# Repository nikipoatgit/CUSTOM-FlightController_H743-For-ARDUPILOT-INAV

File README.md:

# CUSTOM FlightController-H743
The repo contains flight controller target files, PCB Gerber files, and the schematic.

## FC notes 
Nickel-H473 is based on MAMBAH743_V4 FC

However custom pin can be used unless their usage is not compromised , STM programmer IDE can be a great help in case assigning pins.

## FIRMWARE SETUP 

ARDUPILOT : **https://github.com/ArduPilot/ardupilot**

Target Files :`libraries/AP_HAL_ChibiOS/hwdef/`

Environment setup : https://ardupilot.org/dev/docs/building-the-code.html

Build cmd :
```bash
./waf distclean
./Tools/scripts/build_bootloaders.py Nickel407       # Builds bootloader (outputs to Tools/bootloaders/)
./waf configure --board FlyingMoon407
./waf plane
```
bin/hex file are stored in build directory
             
It is recommended to go through ardupilot documentation First

## Target Files 

There are two primary target files ` hwdef-bl.dat (responsible for building bootloader)  
                                        hwdef.dat (for main firmware)`

Checkout this HW files for reference example :   https://github.com/ArduPilot/ardupilot/tree/master/libraries/AP_HAL_ChibiOS/hwdef/fmuv3

### For pin mapping use STM programmer IDE 

## Schematic & PCB 
Check schematic folder  
The pcb is 2 layer 47 * 60 mm

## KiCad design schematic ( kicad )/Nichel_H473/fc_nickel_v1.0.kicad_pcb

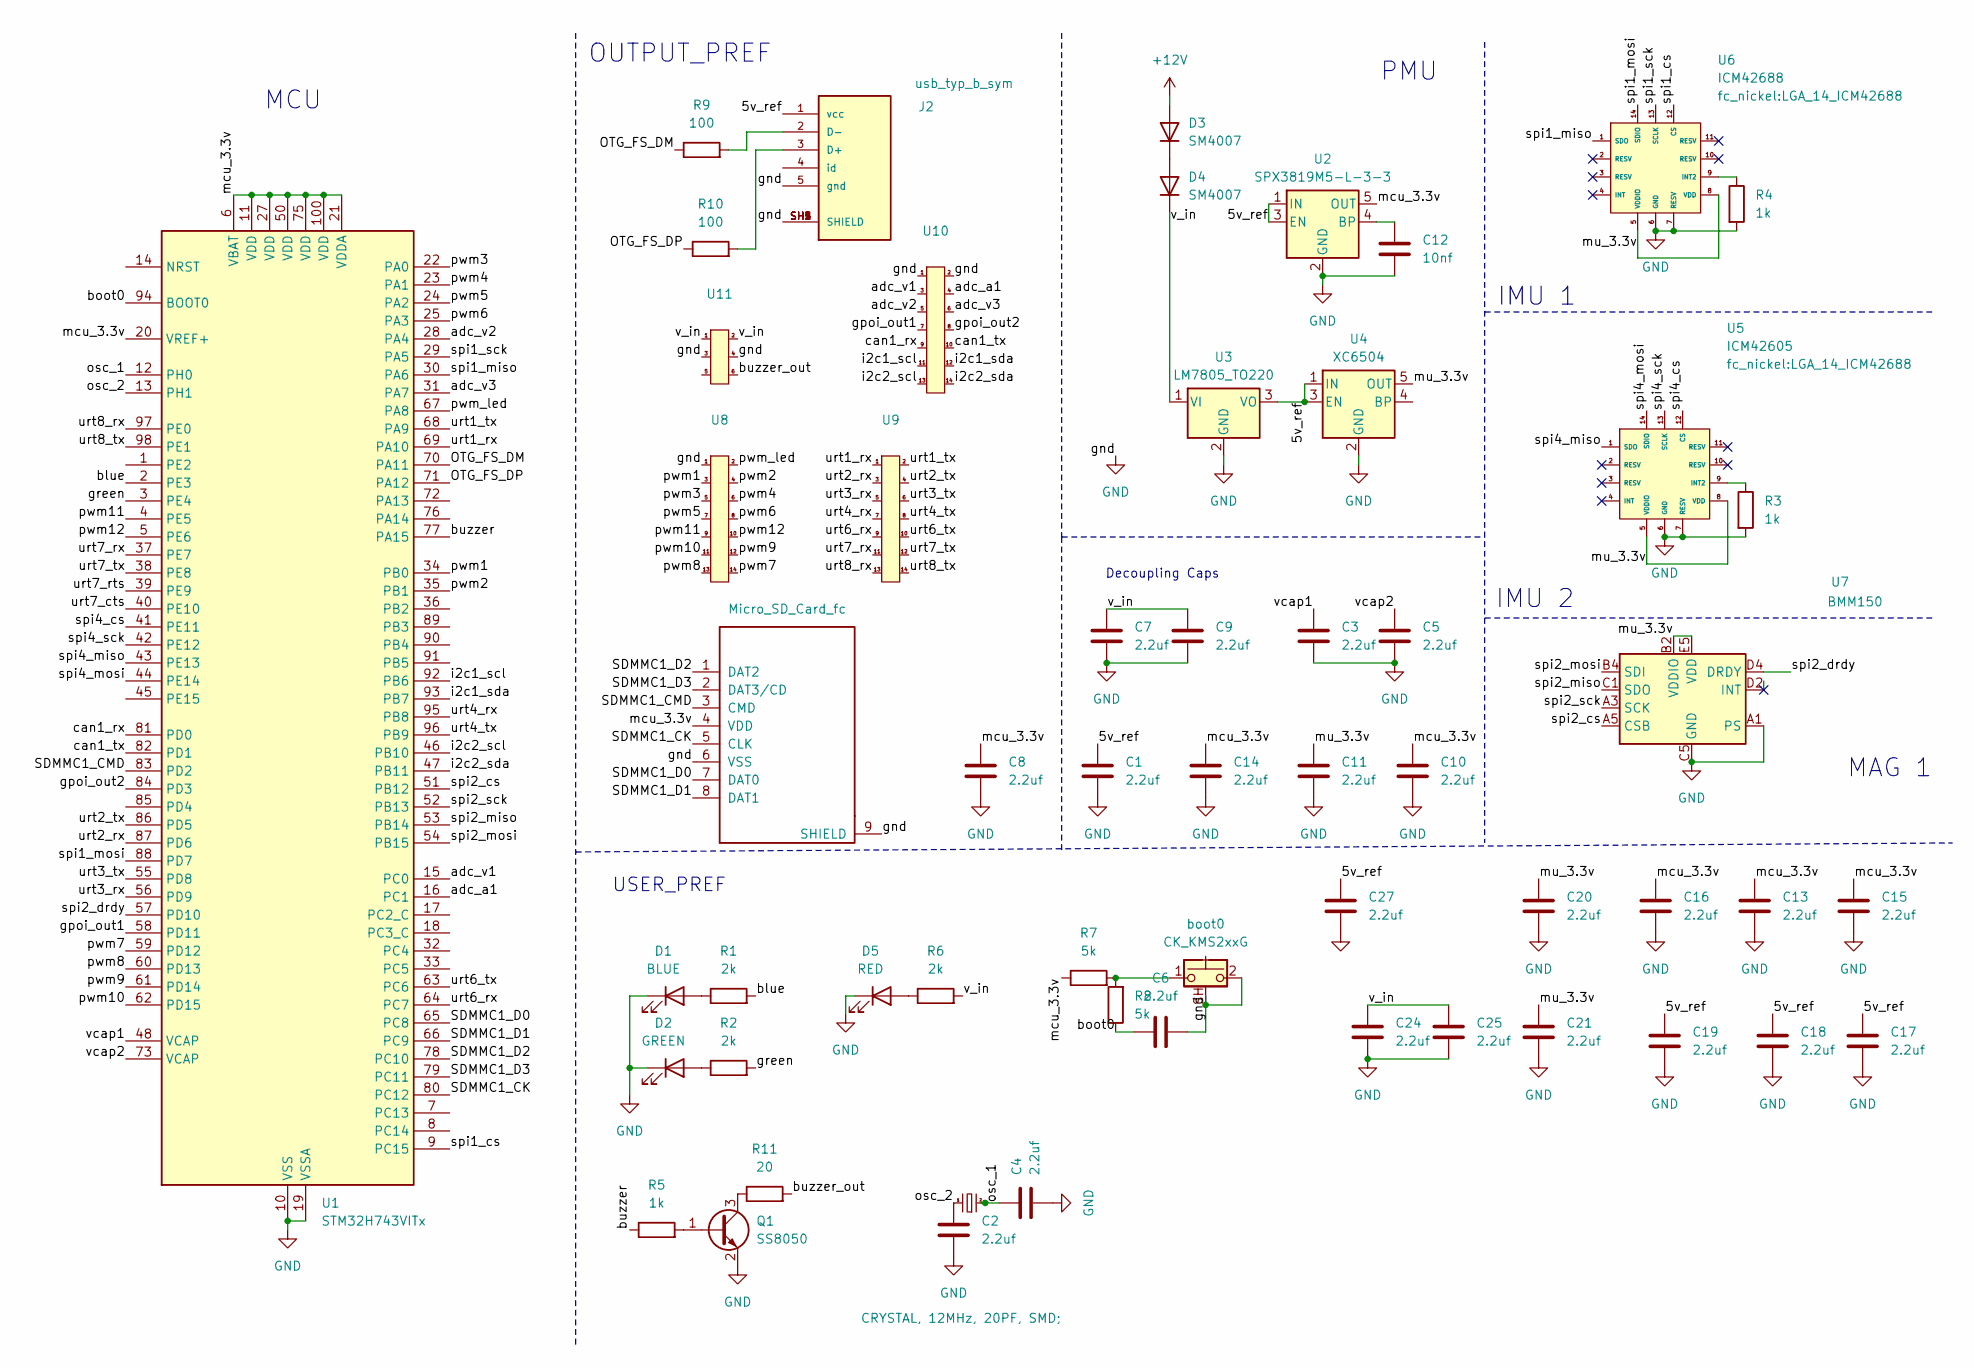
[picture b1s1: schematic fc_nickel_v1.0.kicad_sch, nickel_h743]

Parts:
C1, C2, C3, C4, C5, C6, C7, C8, C9, C10, C11, C13, C14, C15, C16, C17, C18, C19, C20, C21, C24, C25, C27: 2.2uf; C_01005_0402Metric_Pad0.57x0.30mm_HandSolder
C12: 10nf; C_01005_0402Metric_Pad0.57x0.30mm_HandSolder
D1: BLUE; LED_0402_1005Metric
D2: GREEN; LED_0402_1005Metric
D3, D4: SM4007; C_0402_1005Metric
D5: RED; LED_0402_1005Metric
J1: Micro_SD_Card_fc; micro_sdcard_new
J2: usb_typ_b_sym; usb_typ_b; PARTREV 1.0
Q1: SS8050; SOT-23
R1, R2, R6: 2k; R_0402_1005Metric
R3, R4, R5: 1k; R_0402_1005Metric
R7, R8: 5k; R_0402_1005Metric
R9, R10: 100; R_0402_1005Metric
R11: 20; R_0402_1005Metric
U1: STM32H743VITx; LQFP-100_14x14mm_P0.5mm
U2: SPX3819M5-L-3-3; SOT-23-5
U3: LM7805_TO220; TO-220-3_Vertical
U4: XC6504; SOT-23-5
U5: ICM42605; LGA_14_ICM42688
U6: ICM42688; LGA_14_ICM42688
U7: BMM150; WLCSP-12_1.56x1.56mm_P0.4mm
U8: IDC-Header_2x04_P2.54mm_fc
U9, U10: IDC-Header_P2.54mm_fc
U11: IDC-Header_2x03_P2.54mm_fc_power
Y2: CRYSTAL, 12MHz, 20PF, SMD;; XTAL1170X500X450_crystal
boot0: CK_KMS2xxG; SW_SPST_CK_KMS2xxGP

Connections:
+12V: D3.2 (A)
/5v_ref: C1.1, C17.1, C18.1, C19.1, C27.1, J2.1 (vcc), U2.1 (IN), U2.3 (EN), U3.3 (VO), U4.1 (IN), U4.3 (EN)
/OTG_FS_DM: R9.1, U1.70 (PA11)
/OTG_FS_DP: R10.1, U1.71 (PA12)
/SDMMC1_CK: J1.5 (CLK), U1.80 (PC12)
/SDMMC1_CMD: J1.3 (CMD), U1.83 (PD2)
/SDMMC1_D0: J1.7 (DAT0), U1.65 (PC8)
/SDMMC1_D1: J1.8 (DAT1), U1.66 (PC9)
/SDMMC1_D2: J1.1 (DAT2), U1.78 (PC10)
/SDMMC1_D3: J1.2 (DAT3/CD), U1.79 (PC11)
/adc_a1: U1.16 (PC1), U10.4
/adc_v1: U1.15 (PC0), U10.3
/adc_v2: U1.28 (PA4), U10.5
/adc_v3: U1.31 (PA7), U10.6
/blue: R1.2, U1.2 (PE3)
/boot0: C6.1, R8.1, U1.94 (BOOT0)
/buzzer: R5.1, U1.77 (PA15)
/buzzer_out: R11.2, U11.6
/can1_rx: U1.81 (PD0), U10.9
/can1_tx: U1.82 (PD1), U10.10
/gpoi_out1: U1.58 (PD11), U10.7
/gpoi_out2: U1.84 (PD3), U10.8
/green: R2.2, U1.3 (PE4)
/i2c1_scl: U1.92 (PB6), U10.11
/i2c1_sda: U1.93 (PB7), U10.12
/i2c2_scl: U1.46 (PB10), U10.13
/i2c2_sda: U1.47 (PB11), U10.14
/mcu_3.3v: C8.1, C10.1, C13.1, C14.1, C15.1, C16.1, J1.4 (VDD), R7.1, U1.6 (VBAT), U1.11 (VDD), U1.20 (VREF+), U1.21 (VDDA), U1.27 (VDD), U1.50 (VDD), U1.75 (VDD), U1.100 (VDD), U2.5 (OUT); also elsewhere on the board
/mu_3.3v: C11.1, C20.1, C21.1, U4.5 (OUT), U5.5 (VDDIO), U5.8 (VDD), U6.5 (VDDIO), U6.8 (VDD), U7.B2 (VDDIO), U7.E5 (VDD)
/osc_1: C4.1, U1.12 (PH0), Y2.2
/osc_2: C2.1, U1.13 (PH1), Y2.1
/pwm1: U1.34 (PB0), U8.3
/pwm2: U1.35 (PB1), U8.4
/pwm3: U1.22 (PA0), U8.5
/pwm4: U1.23 (PA1), U8.6
/pwm5: U1.24 (PA2), U8.7
/pwm6: U1.25 (PA3), U8.8
/pwm7: U1.59 (PD12), U8.14
/pwm8: U1.60 (PD13), U8.13
/pwm9: U1.61 (PD14), U8.12
/pwm10: U1.62 (PD15), U8.11
/pwm11: U1.4 (PE5), U8.9
/pwm12: U1.5 (PE6), U8.10
/pwm_led: U1.67 (PA8), U8.2
/spi1_cs: U1.9 (PC15), U6.12 (CS)
/spi1_miso: U1.30 (PA6), U6.1 (SDO)
/spi1_mosi: U1.88 (PD7), U6.14 (SDIO)
/spi1_sck: U1.29 (PA5), U6.13 (SCLK)
/spi2_cs: U1.51 (PB12), U7.A5 (CSB)
/spi2_drdy: U1.57 (PD10), U7.D4 (DRDY)
/spi2_miso: U1.53 (PB14), U7.C1 (SDO)
/spi2_mosi: U1.54 (PB15), U7.B4 (SDI)
/spi2_sck: U1.52 (PB13), U7.A3 (SCK)
/spi4_cs: U1.41 (PE11), U5.12 (CS)
/spi4_miso: U1.43 (PE13), U5.1 (SDO)
/spi4_mosi: U1.44 (PE14), U5.14 (SDIO)
/spi4_sck: U1.42 (PE12), U5.13 (SCLK)
/urt1_rx: U1.69 (PA10), U9.1
/urt1_tx: U1.68 (PA9), U9.2
/urt2_rx: U1.87 (PD6), U9.3
/urt2_tx: U1.86 (PD5), U9.4
/urt3_rx: U1.56 (PD9), U9.5
/urt3_tx: U1.55 (PD8), U9.6
/urt4_rx: U1.95 (PB8), U9.7
/urt4_tx: U1.96 (PB9), U9.8
/urt6_rx: U1.64 (PC7), U9.9
/urt6_tx: U1.63 (PC6), U9.10
/urt7_cts: U1.40 (PE10)
/urt7_rts: U1.39 (PE9)
/urt7_rx: U1.37 (PE7), U9.11
/urt7_tx: U1.38 (PE8), U9.12
/urt8_rx: U1.97 (PE0), U9.13
/urt8_tx: U1.98 (PE1), U9.14
/v_in: C7.1, C9.1, C24.1, C25.1, D4.1 (K), R6.2, U3.1 (VI), U11.1, U11.2
/vcap1: C3.2, U1.48 (VCAP)
/vcap2: C5.1, U1.73 (VCAP)
GND: C1.2, C2.2, C3.1, C4.2, C5.2, C6.2, C7.2, C8.2, C9.2, C10.2, C11.2, C12.2, C13.2, C14.2, C15.2, C16.2, C17.2, C18.2, C19.2, C20.2, C21.2, C24.2, C25.2, C27.2, D1.1 (K), D2.1 (K), D5.1 (K), J1.6 (VSS), J1.9 (SHIELD), J2.5 (gnd), J2.SH1 (SHIELD), J2.SH2 (SHIELD), J2.SH3 (SHIELD), J2.SH4 (SHIELD), J2.SH5 (SHIELD), Q1.2 (E), R3.2, R4.2, U1.10 (VSS), U1.19 (VSSA), U1.26 (VSS), U1.49 (VSS), U1.74 (VSS), U1.99 (VSS), U2.2 (GND), U3.2 (GND), U4.2 (GND), U5.6 (GND), U5.7 (RESV), U6.6 (GND), U6.7 (RESV), U7.A1 (PS), U7.C5 (GND), U7.E1 (GND), U7.E3 (GND), U8.1, U10.1, U10.2, U11.3, U11.4, boot0.2, boot0.SH (B); also elsewhere on the board
unnamed: D1.2 (A), R1.1
unnamed: D2.2 (A), R2.1
unnamed: D3.1 (K), D4.2 (A)
unnamed: D5.2 (A), R6.1
unnamed: J2.3 (D+), R10.2
unnamed: J2.2 (D-), R9.2
unnamed: Q1.1 (B), R5.2
unnamed: Q1.3 (C), R11.1
unnamed: R7.2, R8.2, boot0.1
unnamed: C12.1, U2.4 (BP)
unnamed: R3.1, U5.9 (INT2)
unnamed: R4.1, U6.9 (INT2)

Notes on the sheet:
MCU
OUTPUT_PREF
MAG 1
Decoupling Caps
PMU
IMU 2
IMU 1
USER_PREF

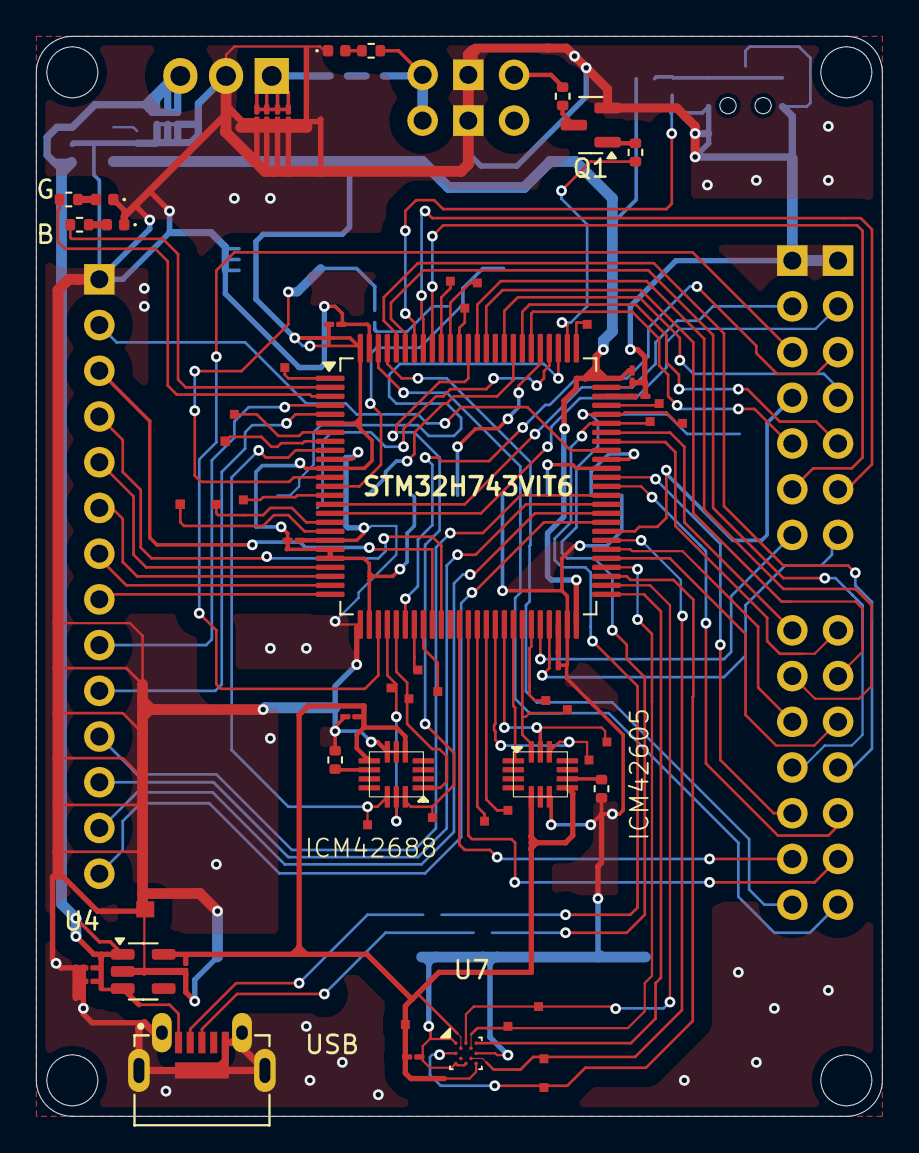
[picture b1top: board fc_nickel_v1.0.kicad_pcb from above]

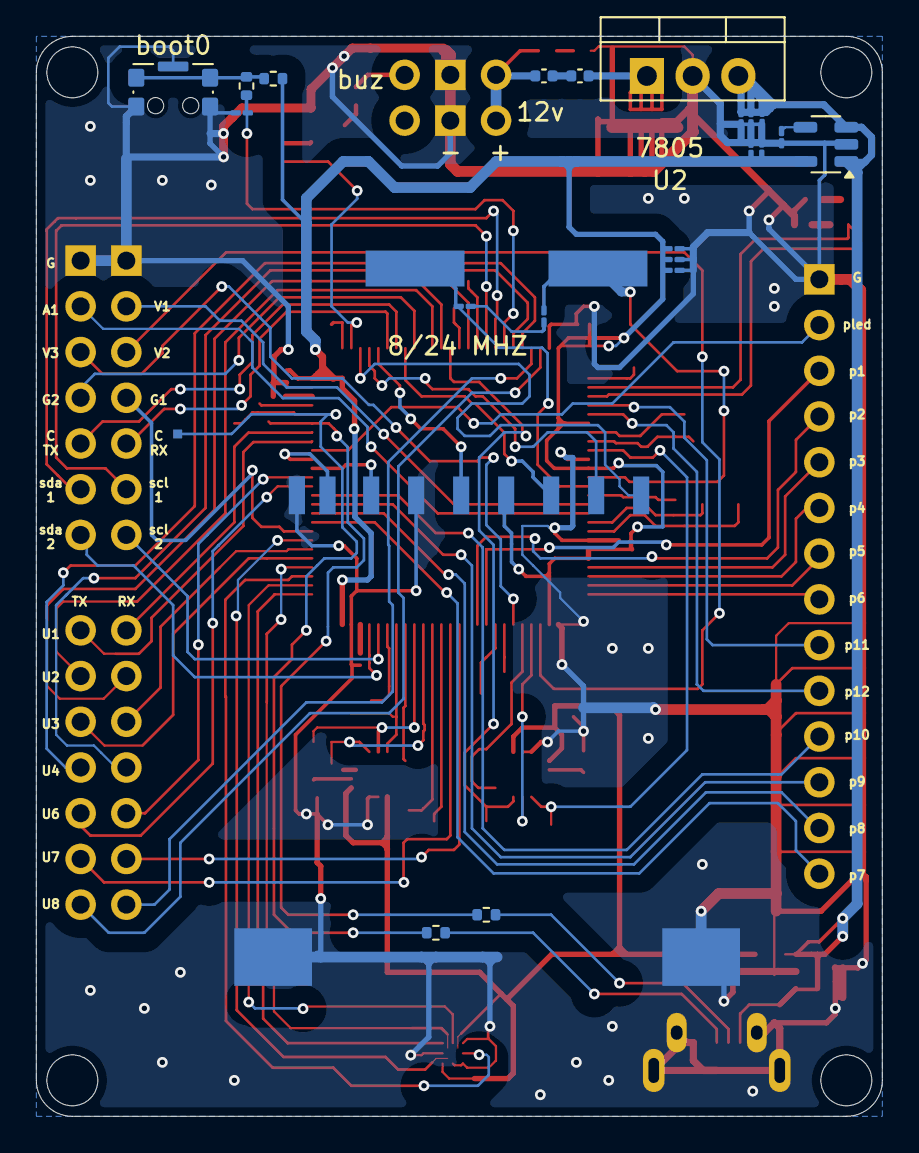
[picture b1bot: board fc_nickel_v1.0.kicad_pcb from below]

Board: 2 copper layers, 47.0 x 60.0 mm, 58 parts (23 on the bottom side), 86 nets.

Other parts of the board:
C13#2, C15#2: 2.2uf; C_01005_0402Metric_Pad0.57x0.30mm_HandSolder

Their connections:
/mcu_3.3v: C13#2.1, C15#2.1; also elsewhere on the board
GND: C13#2.2, C15#2.2; also elsewhere on the board

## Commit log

2025-07-26 files_update
2025-07-26 target files
2025-08-31 updated unconnected crystal ground
    updated unconnected crystal ground
2025-08-31 zip files updated
